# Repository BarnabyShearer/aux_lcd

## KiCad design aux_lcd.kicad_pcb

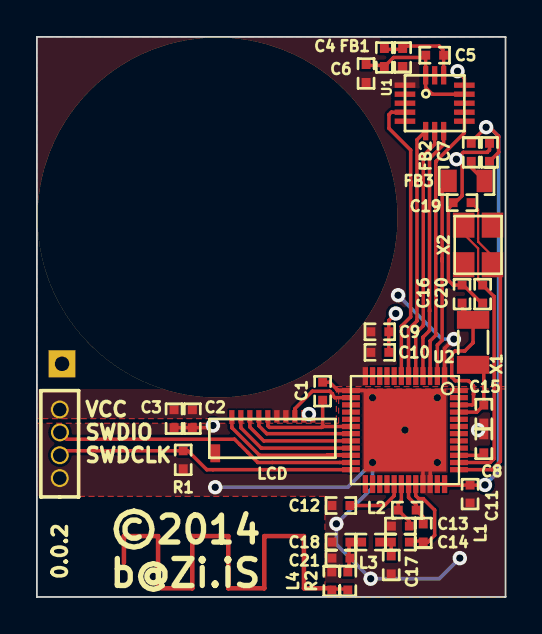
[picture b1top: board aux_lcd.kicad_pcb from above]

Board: 2 copper layers, 26.0 x 31.1 mm, 38 parts (0 on the bottom side), 31 nets.

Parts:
B1: CONN_1; CR2032
B-1: CONN_1; SIL-1
C1, C2, C4, C6, C8, C10: 100nF; SMD-0402_c
C3, C5, C7: 1µF; SMD-0402_c
C9: 4.7µF; SMD-0402_c
C11: 1nF; SMD-0402_c
C12: 47nF; SMD-0402_c
C13: 2.2nF; SMD-0402_c
C14: 2.2pF; SMD-0402_c
C15, C16, C19, C20: 12pF; SMD-0402_c
C17: 0.8pF; SMD-0402_c
C18: 1.5pF; SMD-0402_c
C21: 1pF; SMD-0402_c
FB1: FILTER; SMD-0402
FB2: 15nH; SMD-0402
FB3: 10µH; smd_0805_r
L1: 4.7nH; SMD-0402
L2: 10nH; SMD-0402
L3: 3.3nH; SMD-0402
L4: 1.8nH; SMD-0402
P1: DEBUG; 4-PIN-1.27mm
P2: LCD; FPC10
R1: 12k; SMD-0402_r
R2: 0; SMD-0402_r
U1: ADXL362; LGA16
U2: NRF51822; QFN48
X1: 32.768kHz; FC-13
X2: 16Mhz; crystal_FA238-TSX3225

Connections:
/nRF51822/ANT: L4.2, R2.2
/nRF51822/P0: U1.8, U2.4
/nRF51822/P1: U1.7, U2.5
/nRF51822/P2: U1.6, U2.6
/nRF51822/P3: U1.4, U2.7
/nRF51822/P8: P2.8, U2.14
/nRF51822/P12: C1.1, P2.5, U2.18
/nRF51822/P13: P2.4, U2.19
/nRF51822/P14: P2.3, U2.20
/nRF51822/P15: P2.2, U2.21
/nRF51822/P16: P2.1, U2.22
/nRF51822/P30: U1.9, U2.3
/nRF51822/SWDCLK: P1.2, R1.1, U2.24
/nRF51822/SWDIO: P1.3, U2.23
/nRF51822/VCC: B1.1, C2.1, C3.1, C6.1, C9.1, C10.1, FB1.1, P1.4, P2.6, P2.7, U1.1, U2.1, U2.12
/nRF51822/XC1: C19.1, U2.37, X2.2
/nRF51822/XC2: C20.1, U2.38, X2.1
/nRF51822/XL1: C15.1, U2.45, X1.1
/nRF51822/XL2: C16.1, U2.46, X1.2
GND: B-1.1, C1.2, C2.2, C3.2, C4.2, C5.2, C6.2, C7.2, C8.2, C9.2, C10.2, C11.2, C12.2, C13.2, C15.2, C16.2, C17.2, C18.2, C19.2, C20.2, C21.2, L4.1, P1.1, P2.9, P2.10, R1.2, U1.12, U1.13, U1.16, U2.13, U2.33, U2.34
unnamed: C4.1, C5.1, FB1.2, U1.14
unnamed: C8.1, U2.39
unnamed: C7.1, C11.1, FB2.1, U2.35, U2.36
unnamed: C12.1, U2.29
unnamed: C13.1, L2.2, U2.30
unnamed: C14.1, L1.1, U2.32
unnamed: C14.2, C17.1, L3.2
unnamed: C18.1, C21.1, L3.1, R2.1
unnamed: FB2.2, FB3.1
unnamed: FB3.2, U2.2
unnamed: L1.2, L2.1, U2.31

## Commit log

2014-03-20 Research
2014-03-20 layout
2014-08-31 0.0.2

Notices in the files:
aux_lcd.kicad_pcb:
©2014
